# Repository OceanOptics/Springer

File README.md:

# Springer
Springer is an open source, side scattering optical sensor, utilizing commercially available electronics to measure water turbidity. We aim to create a low cost replicable sensor to be used for oceanographic research.
## Design
### Sensor Head
The sensor is designed for 3 LEDs and a Photodiode receiver. We have been testing LEDS with wavelengths of 650, 670, 720nm with plans to use a 490nm LED in conjunction with a red filter to measure phytoplankton fluorescence. Each LED is 90 degrees to the Photodiode receiver in the middle of the sensor. The head is built with scintillation vials in mind for quick testing and calibration purposes. The cap is designed to be screwed into the head for flow through measurements.

### Electronics
A transimpedance amplifier converts and amplifies current output from the Photodiode into a voltage output readable by an analog to digital converter.  The ADS1115 ADC module is used with an Arduino Nano to control and send data from the sensor to a computer. The signal readings for the three LEDs as well as a dark reading are processed and output by the Arduino through a converter to an RS232 serial bus. The LEDs are switched on and off using the Arduino's digital pins as well as three transistors in common-emitter configuration, allowing for multiple wavelengths to be sampled quickly. Power to the system is controlled by a voltage regulator which accepts input voltage from 7-24 volts.

### Printed Circuit Board
All electronic components are soldered directly to a custom built printed circuit board that can be ordered using the attached files from a variety of PCB manufacturers. A custom circuit board simplifies the design while ensuring all components are properly connected and grounded allowing for quicker assembly as well as a single removable plate that can easily be inserted into and removed from the housing. All components are soldered to the board using through hole pins.

### Housing & Waterproofing
A thick PVC is used as the main housing chamber for the sensor's electronic components. The Sensor head and end cap are attached to the main chamber using fitted O rings to ensure a tight waterproof seal. The sensor head optical pathways are made clear and waterproofed using an epoxy, and shaped using a silicone mold. This helps minimize optical deformities in the epoxy and keep electronics like the LEDs and photodiode sealed. Other 3D printed components are coated with epoxy to ensure no water is leaking into the system and helps improve the rigidity of the components. Wires are fed into the housing using a BLUE ROBOTICS wetlink penetrator.

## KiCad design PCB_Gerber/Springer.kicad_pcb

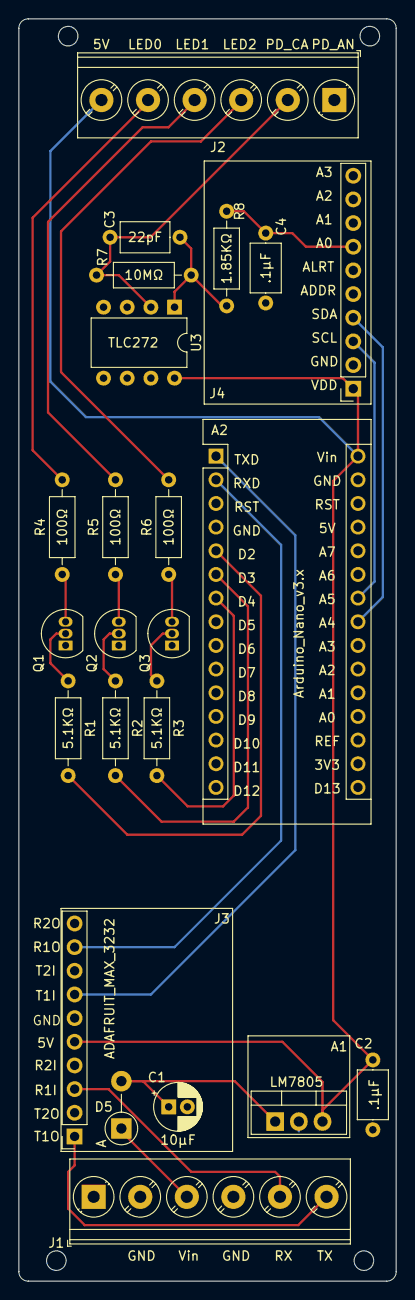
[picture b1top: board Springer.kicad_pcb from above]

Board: 2 copper layers, 40.5 x 135.5 mm, 23 parts (0 on the bottom side), 25 nets.

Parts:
A1: LM7805; TO-220-3_Vertical
A2: Arduino_Nano_v3.x; Arduino_Nano
C1: 10µF; CP_Radial_D5.0mm_P2.00mm
C2, C4: .1µF; C_Axial_L5.1mm_D3.1mm_P7.50mm_Horizontal
C3: 22pF; C_Axial_L5.1mm_D3.1mm_P7.50mm_Horizontal
D5: DIODE; D_DO-41_SOD81_P5.08mm_Vertical_AnodeUp
J1, J2: Screw_Terminal_01x06; TerminalBlock_Phoenix_PT-1,5-6-5.0-H_1x06_P5.00mm_Horizontal
J3: ADAFRUIT_MAX_3232; PinSocket_1x10_P2.54mm_Vertical
J4: ADS1115; PinSocket_1x10_P2.54mm_Vertical
Q1, Q2, Q3: 2N3904; TO-92_Inline
R1, R2, R3: 5.1KΩ; R_Axial_DIN0207_L6.3mm_D2.5mm_P10.16mm_Horizontal
R4, R5, R6: 100Ω; R_Axial_DIN0207_L6.3mm_D2.5mm_P10.16mm_Horizontal
R7: 10MΩ; R_Axial_DIN0207_L6.3mm_D2.5mm_P10.16mm_Horizontal
R8: 1.85KΩ; R_Axial_DIN0207_L6.3mm_D2.5mm_P10.16mm_Horizontal
U3: TLC272; DIP-8_W7.62mm

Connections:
/5V: A1.3 (VO), A2.30 (VIN), C2.2, J2.6, J3.5, J4.1, U3.8 (V+)
/LED0: J2.5, R4.2
/LED1: J2.4, R5.2
/Rx: J1.5, J3.3
/Tx: J1.6, J3.1
/Vin: D5.1 (K), J1.3
GND: A1.2 (GND), A2.29 (GND), C1.2, C2.1, C4.2, J1.2, J1.4, J2.1, J3.6, J4.2, J4.5, Q1.1 (E), Q2.1 (E), Q3.1 (E), U3.3 (+), U3.4 (V-)
unnamed: A1.1 (VI), C1.1, D5.2 (A)
unnamed: A2.1 (D1/TX), J3.7
unnamed: A2.2 (D0/RX), J3.9
unnamed: A2.5 (D2), R1.2
unnamed: A2.6 (D3), R2.2
unnamed: A2.7 (D4), R3.2
unnamed: A2.23 (A4), J4.4
unnamed: A2.24 (A5), J4.3
unnamed: C3.2, R7.1, R8.1, U3.1
unnamed: C4.1, J4.7, R8.2
unnamed: C3.1, J2.2, R7.2, U3.2 (-)
unnamed: J2.3, R6.2
unnamed: Q1.2 (B), R1.1
unnamed: Q1.3 (C), R4.1
unnamed: Q2.2 (B), R2.1
unnamed: Q2.3 (C), R5.1
unnamed: Q3.2 (B), R3.1
unnamed: Q3.3 (C), R6.1

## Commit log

2022-08-16 add PCB, CAD and Arduino IDE files
2022-08-16 add Correct KICAD Project folder for PCB and schematic
2022-08-16 Updated ReadME
    Added electronics, housing and pcb. next add code and more images/info.
2022-08-17 ReadMe Fix and Code edits
2022-08-17 ReadMe Fix, bill of materials and Code edits
2022-08-17 ReadME re-add
2022-08-22 Add assembly & soldering guide and head key.stl
2022-09-02 Organizing - added a gitignore and an f3d file
